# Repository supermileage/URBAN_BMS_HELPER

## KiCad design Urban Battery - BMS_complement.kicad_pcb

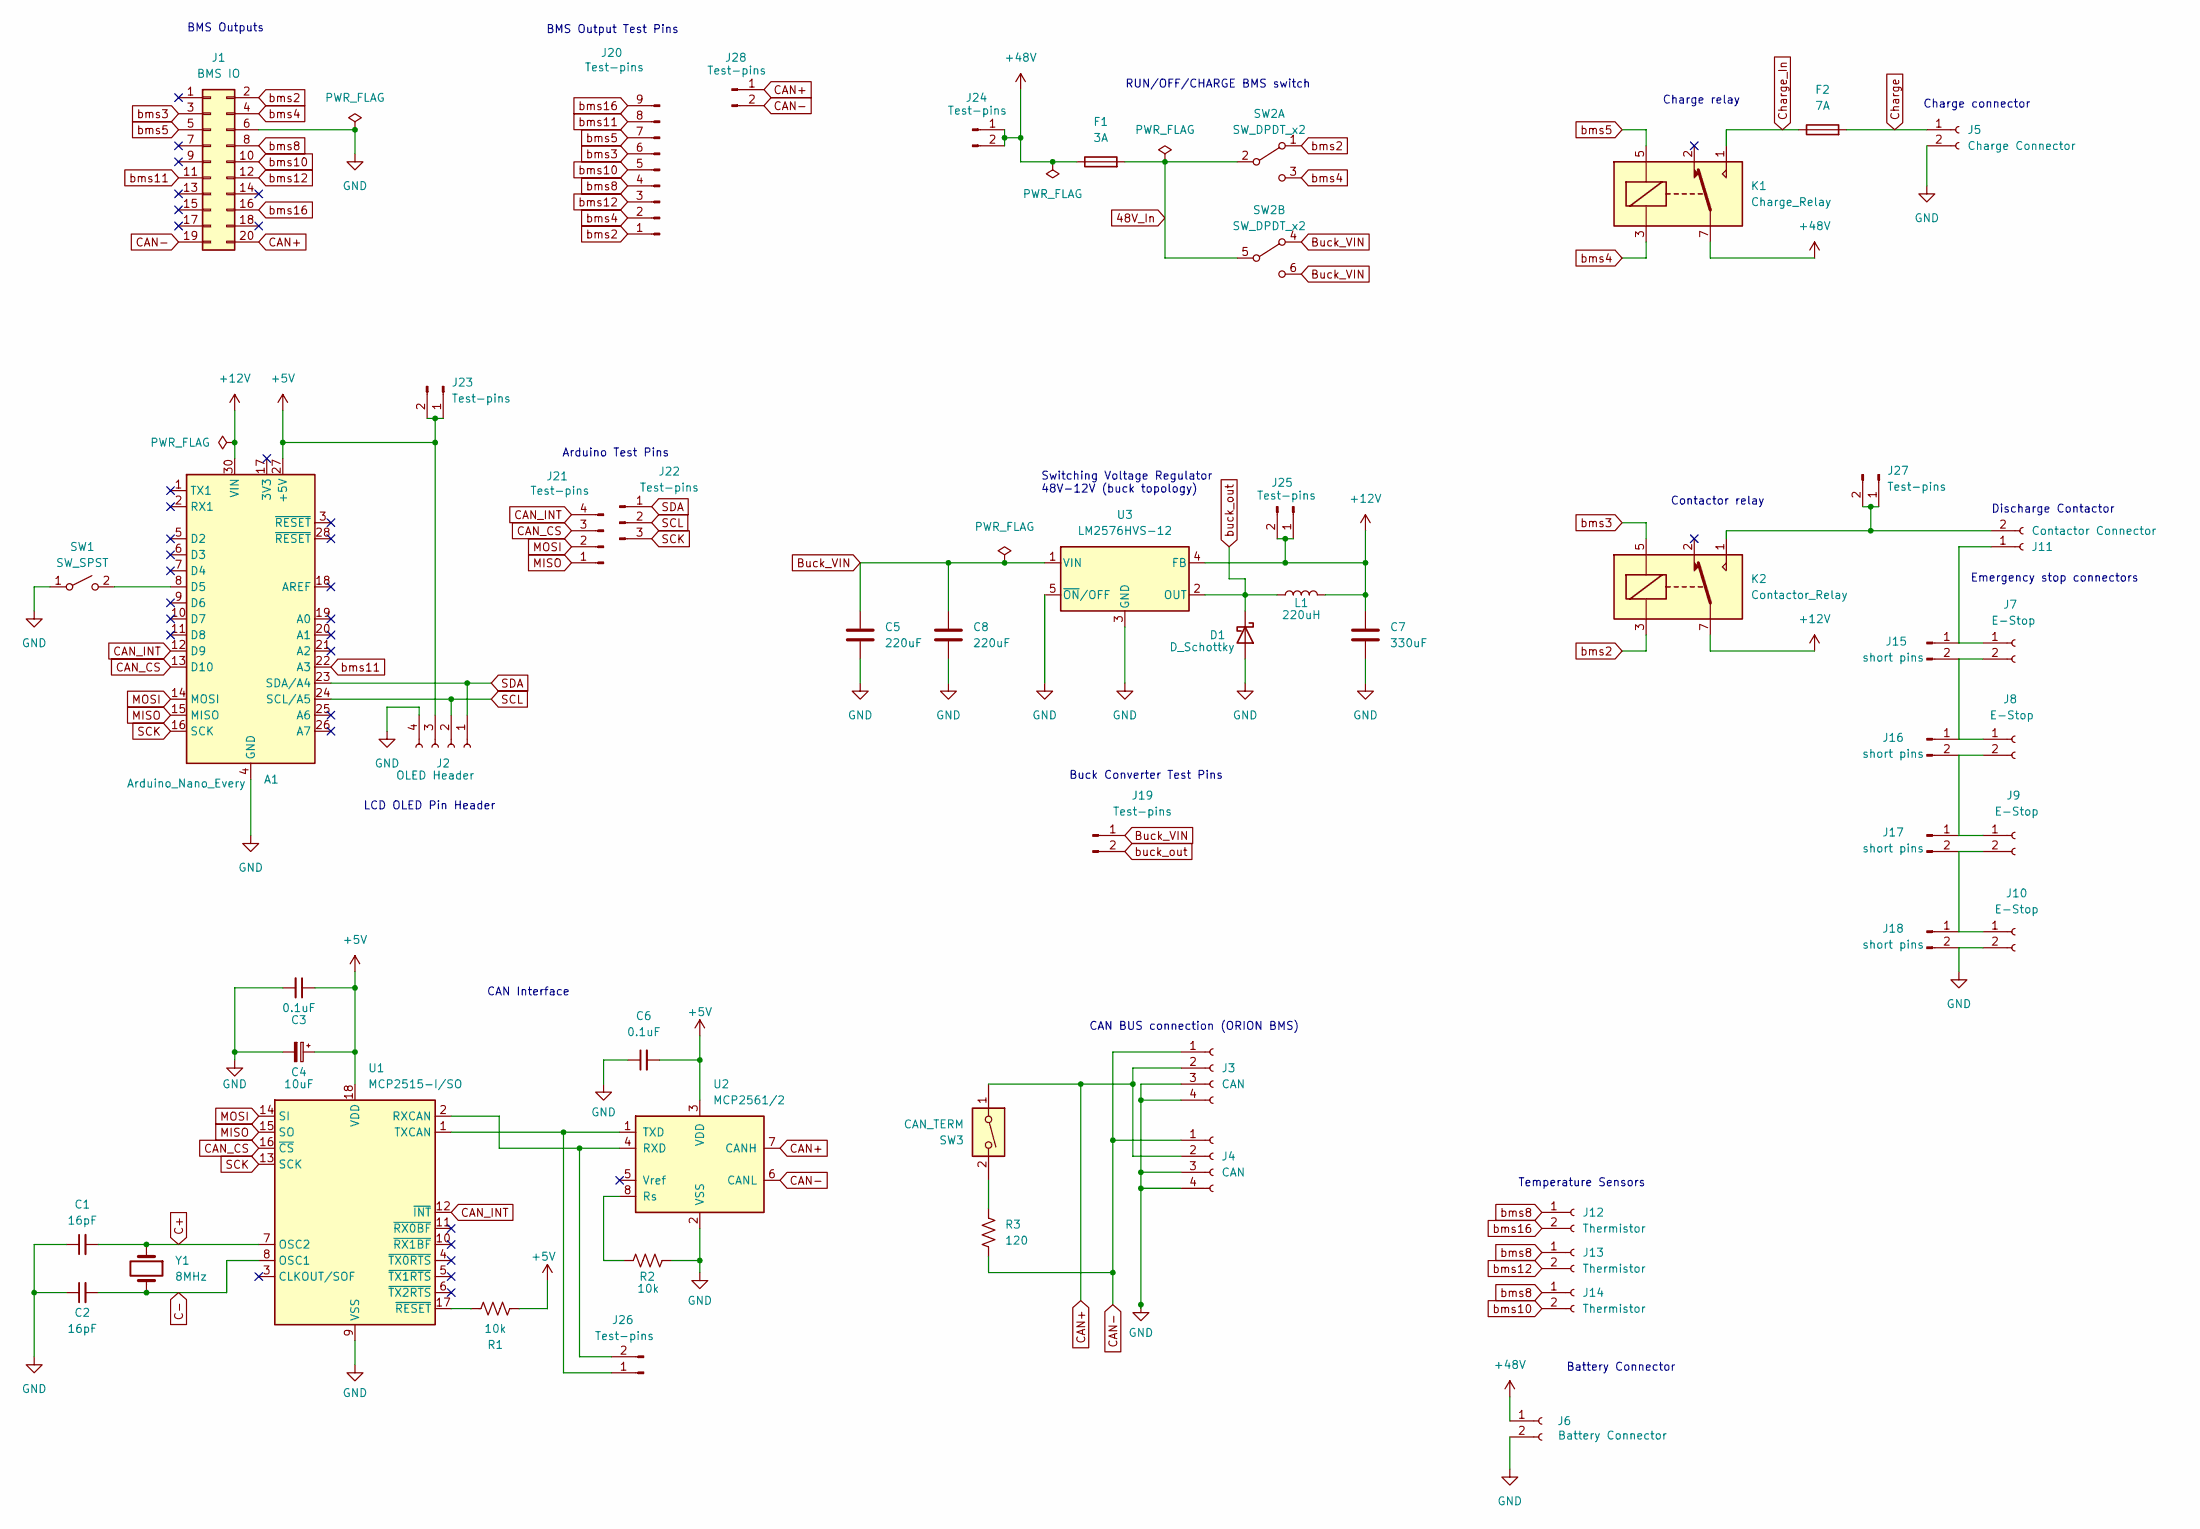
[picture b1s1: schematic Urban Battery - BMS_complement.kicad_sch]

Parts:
A1: Arduino_Nano_Every; Arduino_Nano
C1, C2: 16pF; C_0805_2012Metric_Pad1.18x1.45mm_HandSolder
C3, C6: 0.1uF; C_0805_2012Metric_Pad1.18x1.45mm_HandSolder
C4: 10uF; CP_Radial_D10.0mm_P5.00mm
C5, C8: 220uF; C_Radial_D12.5mm_H25.0mm_P5.00mm
C7: 330uF; CP_Elec_10x10.5
D1: D_Schottky; D_DO-201AD_P15.24mm_Horizontal
F1: 3A; Fuseholder_Blade_Mini_Keystone_3568
F2: 7A; Fuseholder_Blade_Mini_Keystone_3568
J1: BMS IO; B20BPADSS1FLFSN
J2: OLED Header; OLED_Header
J3, J4: CAN; Molex_Mini-Fit_Jr_5569-04A2_2x02_P4.20mm_Horizontal
J5: Charge Connector; Molex_Mini-Fit_Jr_5569-02A2_2x01_P4.20mm_Horizontal
J6: Battery Connector; Molex_Mini-Fit_Jr_5569-02A2_2x01_P4.20mm_Horizontal
J7, J8, J9, J10: E-Stop; Molex_Mini-Fit_Jr_5569-02A2_2x01_P4.20mm_Horizontal
J11: Contactor Connector; TerminalBlock_Phoenix_MKDS-1,5-2-5.08_1x02_P5.08mm_Horizont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
J12, J13, J14: Thermistor; TerminalBlock_Phoenix_MKDS-1,5-2-5.08_1x02_P5.08mm_Horizont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
J15, J16, J17, J18: short pins; PinHeader_1x02_P2.54mm_Vertical
J19, J23, J24, J25, J26, J27, J28: Test-pins; PinHeader_1x02_P2.54mm_Vertical
J20: Test-pins; PinHeader_1x09_P2.54mm_Vertical
J21: Test-pins; PinHeader_1x04_P2.54mm_Vertical
J22: Test-pins; PinHeader_1x03_P2.54mm_Vertical
K1: Charge_Relay; Relay_RT334048
K2: Contactor_Relay; Relay_RT334048
L1: 220uH; Inductor_PE-52629NL
R1, R2: 10k; R_0805_2012Metric_Pad1.20x1.40mm_HandSolder
R3: 120; R_0805_2012Metric_Pad1.20x1.40mm_HandSolder
SW1: SW_SPST; SW_Tactile_SPST_Angled_PTS645Vx31-2LFS
SW2: SW_DPDT_x2; Toggle_Switch_M2022S2A2W30
SW3: CAN_TERM; PinHeader_1x02_P2.54mm_Horizontal
U1: MCP2515-I/SO; SOIC-18W_7.5x11.6mm_P1.27mm
U2: MCP2561/2; SOIC-8_3.9x4.9mm_P1.27mm
U3: LM2576HVS-12; TO-263-5_TabPin3
Y1: 8MHz; Crystal_HC49-U_Vertical

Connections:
48V_In: F1.2, SW2.2 (B), SW2.5 (B)
+5V: A1.27 (+5V), C3.1, C4.1, C6.2, J2.3, J23.1, J23.2, R1.1, U1.18 (VDD), U2.3 (VDD)
+12V: A1.30 (VIN), C7.1, J25.1, J25.2, K2.7, L1.2, U3.4 (FB)
+48V: F1.1, J6.1, J24.1, J24.2, K1.7
Buck_VIN: C5.1, C8.1, J19.1, SW2.4 (A), SW2.6 (C), U3.1 (VIN)
C+: C1.2, U1.7 (OSC2), Y1.1
C-: C2.2, U1.8 (OSC1), Y1.2
CAN+: J1.20, J3.2, J4.2, J28.1, SW3.1, U2.7 (CANH)
CAN-: J1.19, J3.1, J4.1, J28.2, R3.2, U2.6 (CANL)
CAN_CS: A1.13 (D10), J21.3, U1.16 (~CS)
CAN_INT: A1.12 (D9), J21.4, U1.12 (~INT)
Charge: F2.2, J5.1
Charge_In: F2.1, K1.1
GND: A1.4 (GND), A1.29 (GND), C1.1, C2.1, C3.2, C4.2, C5.2, C6.1, C7.2, C8.2, D1.2 (A), J1.6, J2.4, J3.3, J3.4, J4.3, J4.4, J5.2, J6.2, J10.2, J18.2, R2.2, SW1.1 (A), U1.9 (VSS), U2.2 (VSS), U3.3 (GND), U3.5 (~ON/OFF)
MISO: A1.15 (MISO), J21.1, U1.15 (SO)
MOSI: A1.14 (MOSI), J21.2, U1.14 (SI)
unnamed: A1.8 (D5), SW1.2 (B)
unnamed: J9.2, J10.1, J17.2, J18.1
unnamed: J7.1, J11.1, J15.1
unnamed: J11.2, J27.1, J27.2, K2.1
unnamed: J7.2, J8.1, J15.2, J16.1
unnamed: J8.2, J9.1, J16.2, J17.1
unnamed: J26.1, U1.1 (TXCAN), U2.1 (TXD)
unnamed: J26.2, U1.2 (RXCAN), U2.4 (RXD)
unnamed: R3.1, SW3.2
unnamed: R1.2, U1.17 (~RESET)
unnamed: R2.1, U2.8 (Rs)
SCK: A1.16 (SCK), J22.3, U1.13 (SCK)
SCL: A1.24 (SCL/A5), J2.2, J22.2
SDA: A1.23 (SDA/A4), J2.1, J22.1
bms2: J1.2, J20.1, K2.3, SW2.1 (A)
bms3: J1.3, J20.6, K2.5
bms4: J1.4, J20.2, K1.3, SW2.3 (C)
bms5: J1.5, J20.7, K1.5
bms8: J1.8, J12.1, J13.1, J14.1, J20.4
bms10: J1.10, J14.2, J20.5
bms11: A1.22 (A3), J1.11, J20.8
bms12: J1.12, J13.2, J20.3
bms16: J1.16, J12.2, J20.9
buck_out: D1.1 (K), J19.2, L1.1, U3.2 (OUT)

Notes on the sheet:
Charge connector
Contactor relay
Buck Converter Test Pins
Temperature Sensors
Switching Voltage Regulator 48V-12V (buck topology)
Charge relay
RUN/OFF/CHARGE BMS switch
BMS Outputs
CAN BUS connection (ORION BMS)
BMS Output Test Pins
Emergency stop connectors
Battery Connector
Arduino Test Pins
LCD OLED Pin Header
Discharge Contactor
CAN Interface

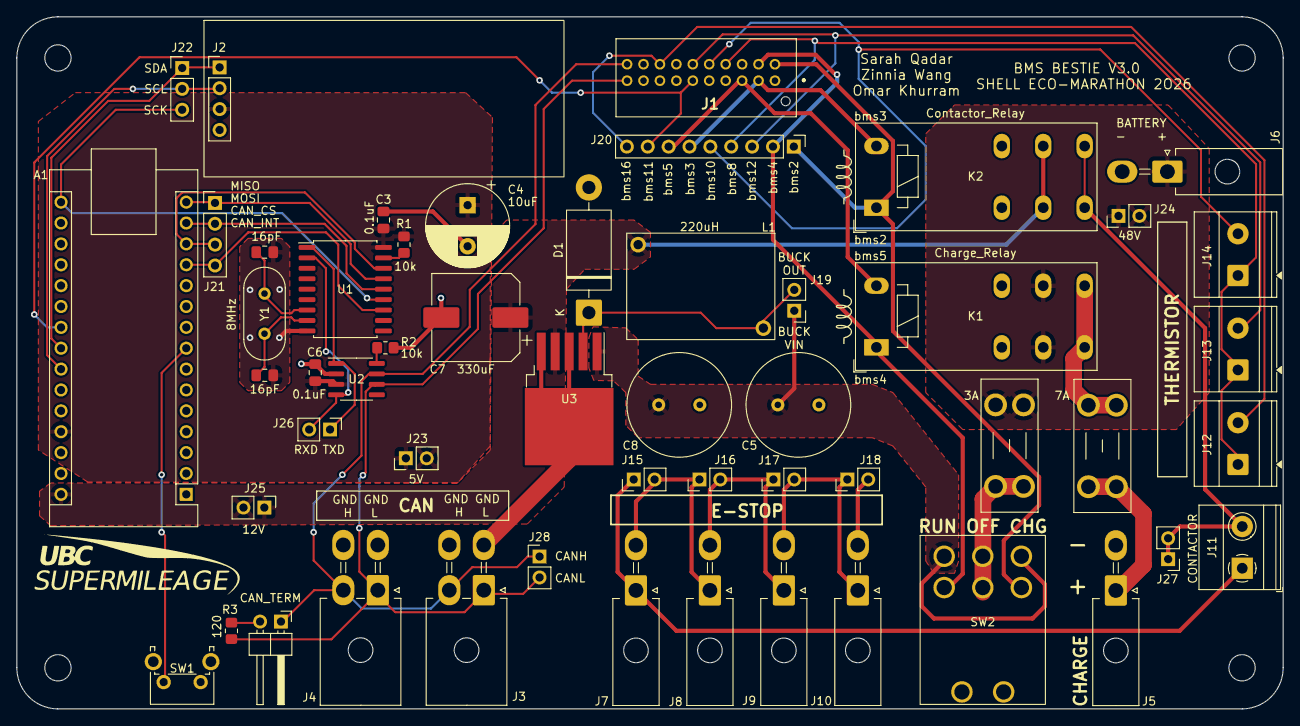
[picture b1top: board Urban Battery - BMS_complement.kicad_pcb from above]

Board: 2 copper layers, 154.1 x 84.2 mm, 53 parts (0 on the bottom side), 40 nets.

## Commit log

2022-10-22 Started PCB schematic
2022-10-22 generic schematic created
2022-10-29 Added to schematic and assigned some footprints
2022-11-05 Schematic updates and added custom footprint library
2022-11-06 CAN interface added, fixed all electrical errors, added some footprints
2022-11-08 added pushbutton and OLED LCD circuit to arduino
2022-11-10 Added temporary footprints and preliminary layout
2022-11-10 Edited component placement
2022-11-11 reorganized layout, started routing traces and added supermileage logo
2022-11-12 added can_int, changed oled button, added 4th safety switch
2022-11-12 updated layout from schematic, deleted traces
2022-11-13 First layout complete
2022-11-14 Layout updated
2022-11-14 moved supermileage logo
2022-11-16 Updated traces
2022-11-25 switched 12V charge and contactor relays for 48V relays, updated symbol and footprint accordingly
2022-11-26 Updated components and layout
2022-11-26 updated schematic, added new footprints etc
2022-11-28 specced R1, R2, C3, C6 and R3, updated schematic with their datasheets
2022-12-03 Reassigned inductor footprint
2022-12-03 fixed relay symbols
2022-12-04 Updated C4, added differential pairs to CAN
2022-12-14 Updated silkscreen, added test points
2022-12-25 updated component datasheets
2022-12-26 Updated relays & silkscreen
2022-12-30 generated gerbers
2023-01-01 added datasheets for tactile switch and OLED header
2023-02-27 swapped run and charge labels, changed charge connector, renamed board
2023-03-02 added downloaded footprint for bms i/o, updated on layout. fixed orientation of charge connector labels
2023-03-03 fixed errors brought up by DRC on pcb
2023-03-04 generated gerbers and drill file in gerbers2.0
2024-10-12 only pushing to verify no accidental changes were made before more people work on this again
2024-10-16 updated connector footprints of J6 and J12-J14
2024-10-16 updated J13, J14 footprints and datasheets to match J12
2025-11-01 Added new CAN and killswitch connector DigiKey symbols
2025-11-01 Update footprints for CAN and killswitch connectors
2025-11-03 Added test pin headers for BMS output, killswitches, Arduino and Buck converter
2025-11-07 added debug headers
2025-11-20 Revised layout with new test pin & connector footprints, altered board shape
2025-11-21 Fixed up some more stuff in schematic
2025-11-21 shifted regulator circuit and relay to the left to accomodate new longer minifit connectors. added 48V, 12V, 5V fill zones
2025-11-22 routed BMS test pins, edited some labels
2025-11-22 resolving minor overlap and clearance issues
2025-11-24 Cleaned up labelling, overlap and logo; GND plane connections remain sus
2025-11-29 Added labels to contactor pins to aid in probing bms signals
2025-12-01 revised CAN connector pinout to match CAN accessories board; rerouted CAN+, confirmed old RUN/OFF/CHG switch custom footprint will work with new specced switch
2025-12-02 added chamfered edges on fill zones. fixed issue of GND fill zone on crystal, and also fixed GND pin on BMS I/O being cut-off from the GND plane
2025-12-02 minor changes
2025-12-02 rerouting around CAN circuit to avoid cutting into the GND plane, rerouted bms11 (SoC from BMS) to go straight between arduino and BMS I/O
2025-12-03 changed silkscreen labels to be horizontal, added labels for test pin headers in top left corner, rounded corners of board edge cut, added updated gerber files
2025-12-04 added footprints for switch options
2026-01-10 most recent version
